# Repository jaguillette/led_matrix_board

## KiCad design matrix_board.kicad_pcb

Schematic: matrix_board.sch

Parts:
C1: 1uF; fab-C1206
J1: MATRIX_CONNECTOR; fab-2X08SMD
JP1: ISP; fab-2X03SMD
M1: PWR_LED; fab-LED1206
M2: LED; fab-LED1206
M3: PINHD-2X2-SMD; fab-2X02SMD
M4: RESONATOR; fab-EFOBM
R1: 499; fab-R1206
R2: RES-US1206; fab-R1206
R3: 10k; fab-R1206
S1: PD0_SWITCH; fab-6MM_SWITCH
S2: PD1_SWITCH; fab-6MM_SWITCH
U1: ATmega328P-AU; fab-TQFP32-08THIN

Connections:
A: J1.9, U1.23 (PC0)
B: J1.10, U1.24 (PC1)
B1: J1.3, U1.2 (PD4)
B2: J1.7, U1.11 (PD7)
C: J1.11, U1.25 (PC2)
CLK: J1.13, U1.12 (PB0)
D: J1.12, U1.26 (PC3)
G1: J1.2, U1.1 (PD3)
G2: J1.6, U1.10 (PD6)
GROUND: C1.1, J1.4, J1.8, J1.16, JP1.6, M1.2 (C), M2.2 (C), M3.2, M3.4, U1.3 (GND), U1.5 (GND), U1.21 (GND)
LAT: J1.14, U1.14 (PB2)
MISO: JP1.1, U1.16 (PB4)
MOSI: JP1.4, U1.15 (PB3)
unnamed: M1.1 (A), R1.2
unnamed: M2.1 (A), R2.2
OE: J1.15, U1.13 (PB1)
PD0: S1.3 (S), U1.30 (PD0)
PD1: S2.3 (S), U1.31 (PD1)
R1: J1.1, U1.32 (PD2)
R2: J1.5, U1.9 (PD5)
RESET: JP1.5, R3.2, U1.29 (~RESET~/PC6)
SCK: JP1.3, U1.17 (PB5)
TEST: R2.1, U1.27 (PC4)
VCC: C1.2, JP1.2, M3.1, M3.3, R1.1, R3.1, S1.1, S2.1, U1.4 (VCC), U1.6 (VCC), U1.18 (AVCC)

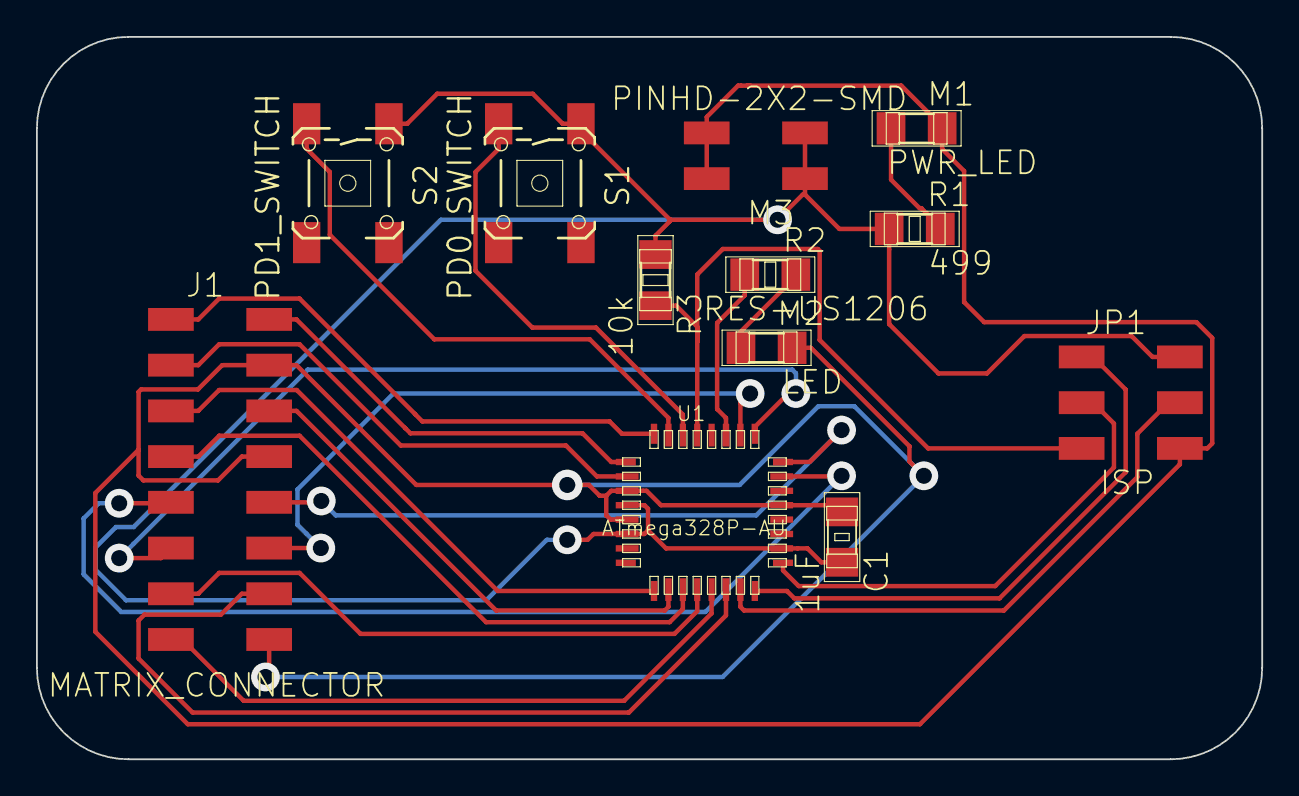
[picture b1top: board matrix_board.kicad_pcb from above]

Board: 2 copper layers, 68.1 x 40.1 mm, 12 parts (0 on the bottom side), 24 nets.

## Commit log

2018-12-09 updated board
2018-12-15 commit before milling
2018-12-15 added more accurate rivets
2018-12-16 added new board design. hope it works
2018-12-16 remade board to be bigger
2018-12-17 updated board with more components so it'll work
    added pull up resistor on reset and clock on xtal, also moved capacitor closer to chip
2018-12-17 added frame for matrix
